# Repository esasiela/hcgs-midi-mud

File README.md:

# hcgs-midi-mud

This is the firmware, schematics, and artwork files for an Arduino-based MIDI Step Sequencer.

Details about the behavior, design, software, and hardware are at [Hedge Court](https://www.hedgecourt.com/robots/grumpenspiel/midi-mud/).

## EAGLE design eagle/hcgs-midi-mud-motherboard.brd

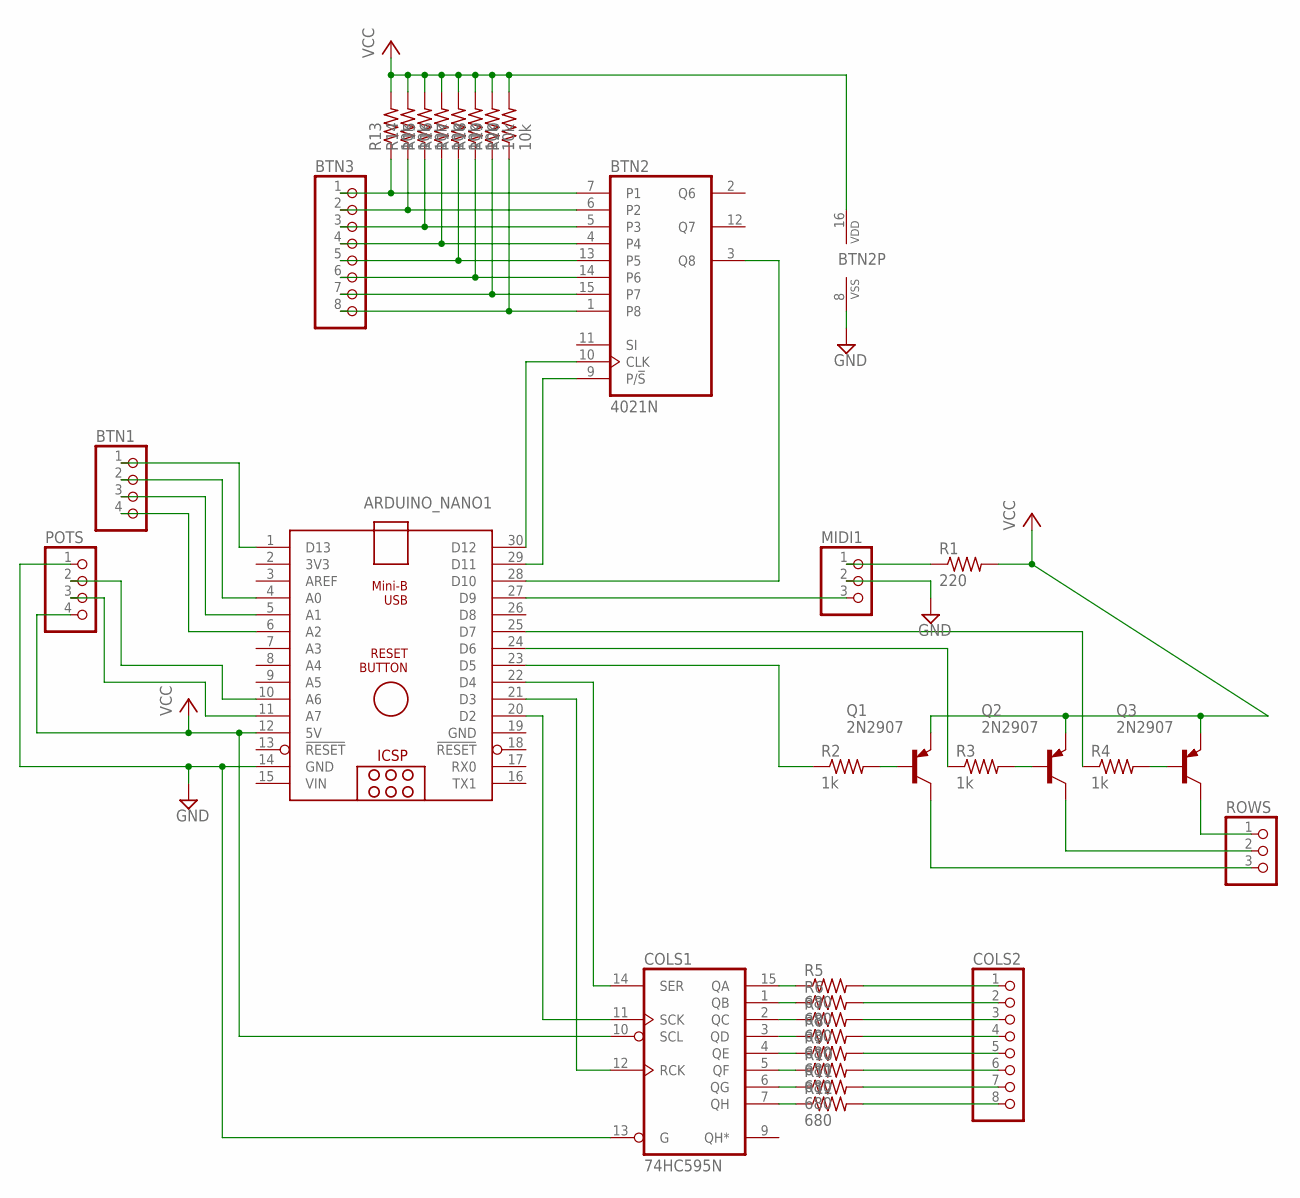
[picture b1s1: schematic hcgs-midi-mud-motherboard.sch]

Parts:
ARDUINO_NANO1: ARDUINO_NANO_HCARDUINO_NANO_NO_HOLE; ARDUINO_NANO_NO_HOLE
BTN1: PINHD-1X4; 1X04
BTN2: 4021N; DIL16
BTN3: PINHD-1X8; 1X08
COLS1: 74HC595N; DIL16
COLS2: PINHD-1X8; 1X08
MIDI1: PINHD-1X3; 1X03
POTS: PINHD-1X4; 1X04
Q1, Q2, Q3: 2N2907; TO92-EBC-OVAL
R1: 220; 0309/12
R2, R3, R4: 1k; 0309/12
R5, R6, R7, R8, R9, R10, R11, R12: 680; 0309/12
R13, R14, R15, R16, R17, R18, R19, R20: 10k; 0309/12
ROWS: PINHD-1X3; 1X03

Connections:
GND: ARDUINO_NANO1.14 (GND), ARDUINO_NANO1.19 (GND), BTN2.8 (VSS), COLS1.8 (GND), COLS1.13 (G), MIDI1.2, POTS.1
unnamed: ARDUINO_NANO1.1 (D13), BTN1.1
unnamed: ARDUINO_NANO1.4 (A0), BTN1.2
unnamed: ARDUINO_NANO1.11 (A7), POTS.3
unnamed: ARDUINO_NANO1.10 (A6), POTS.2
unnamed: ARDUINO_NANO1.5 (A1), BTN1.3
unnamed: ARDUINO_NANO1.6 (A2), BTN1.4
unnamed: Q1.B, R2.2
unnamed: MIDI1.1, R1.1
unnamed: Q2.B, R3.2
unnamed: ARDUINO_NANO1.27 (D9), MIDI1.3
unnamed: Q3.B, R4.2
unnamed: ARDUINO_NANO1.23 (D5), R2.1
unnamed: ARDUINO_NANO1.24 (D6), R3.1
unnamed: ARDUINO_NANO1.25 (D7), R4.1
unnamed: Q1.C, ROWS.3
unnamed: Q2.C, ROWS.2
unnamed: Q3.C, ROWS.1
unnamed: COLS1.15 (QA), R5.1
unnamed: COLS1.1 (QB), R6.1
unnamed: COLS1.2 (QC), R7.1
unnamed: COLS1.3 (QD), R8.1
unnamed: COLS1.4 (QE), R9.1
unnamed: COLS1.5 (QF), R10.1
unnamed: COLS1.6 (QG), R11.1
unnamed: COLS1.7 (QH), R12.1
unnamed: COLS2.1, R5.2
unnamed: COLS2.2, R6.2
unnamed: COLS2.3, R7.2
unnamed: COLS2.4, R8.2
unnamed: COLS2.5, R9.2
unnamed: COLS2.6, R10.2
unnamed: COLS2.7, R11.2
unnamed: COLS2.8, R12.2
unnamed: ARDUINO_NANO1.20 (D2), COLS1.11 (SCK)
unnamed: ARDUINO_NANO1.21 (D3), COLS1.12 (RCK)
unnamed: BTN2.1 (P8), BTN3.8, R20.1
unnamed: ARDUINO_NANO1.22 (D4), COLS1.14 (SER)
unnamed: BTN2.15 (P7), BTN3.7, R19.1
unnamed: BTN2.14 (P6), BTN3.6, R18.1
unnamed: BTN2.13 (P5), BTN3.5, R17.1
unnamed: BTN2.4, BTN3.4, R16.1
unnamed: BTN2.5 (P3), BTN3.3, R15.1
unnamed: BTN2.6 (P2), BTN3.2, R14.1
unnamed: BTN2.7 (P1), BTN3.1, R13.1
unnamed: ARDUINO_NANO1.30 (D12), BTN2.10 (CLK)
unnamed: ARDUINO_NANO1.28 (D10), BTN2.3 (Q8)
unnamed: ARDUINO_NANO1.29 (D11), BTN2.9 (P/!S)
VCC: ARDUINO_NANO1.12 (5V), BTN2.16 (VDD), COLS1.10 (SCL), COLS1.16 (VCC), POTS.4, Q1.E, Q2.E, Q3.E, R1.2, R13.2, R14.2, R15.2, R16.2, R17.2, R18.2, R19.2, R20.2
VIN: ARDUINO_NANO1.15 (VIN)

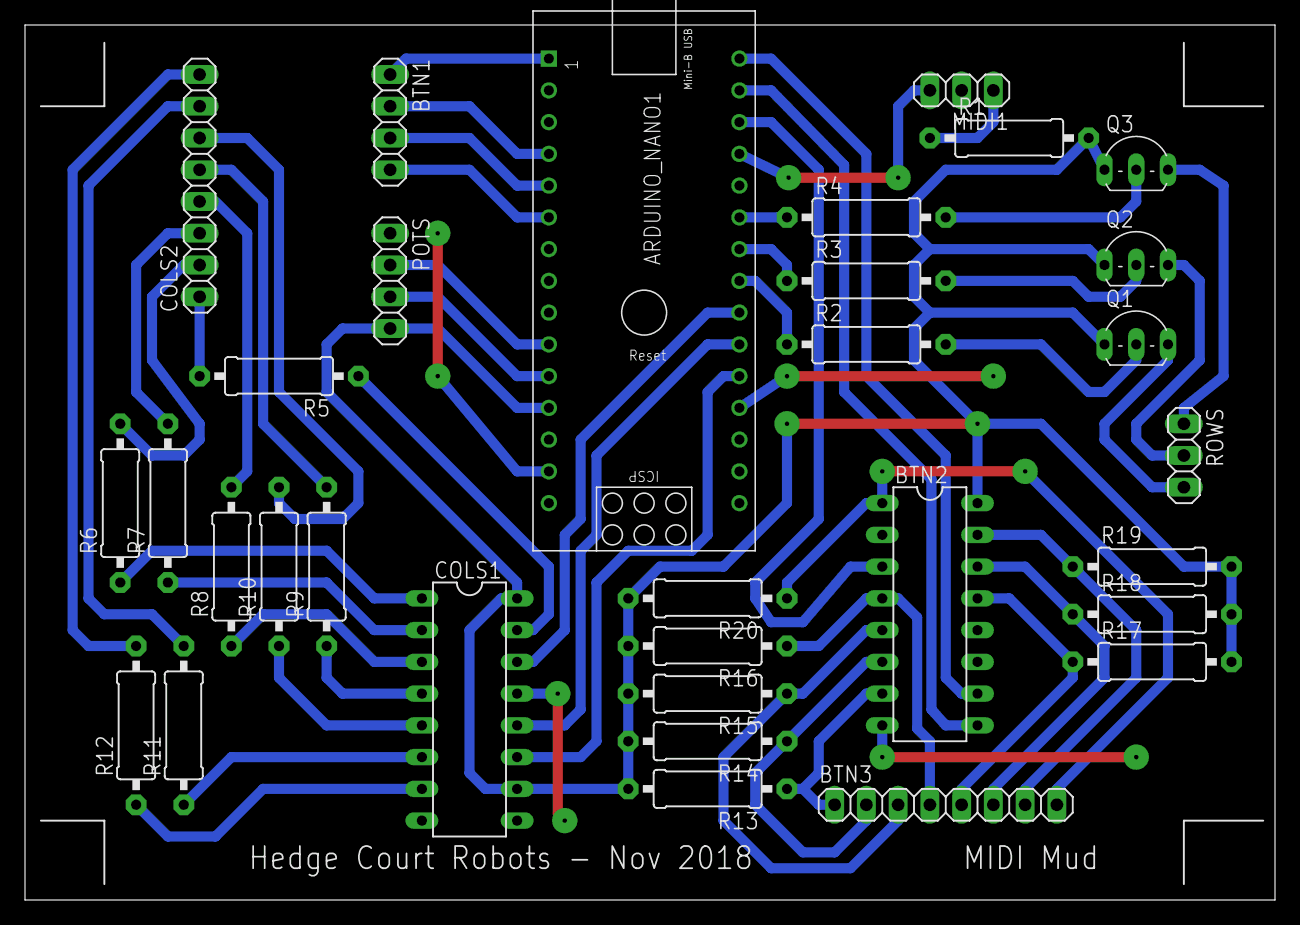
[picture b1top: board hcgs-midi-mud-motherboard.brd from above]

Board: 2 copper layers, 100.0 x 70.0 mm, 32 parts (0 on the bottom side), 49 nets.

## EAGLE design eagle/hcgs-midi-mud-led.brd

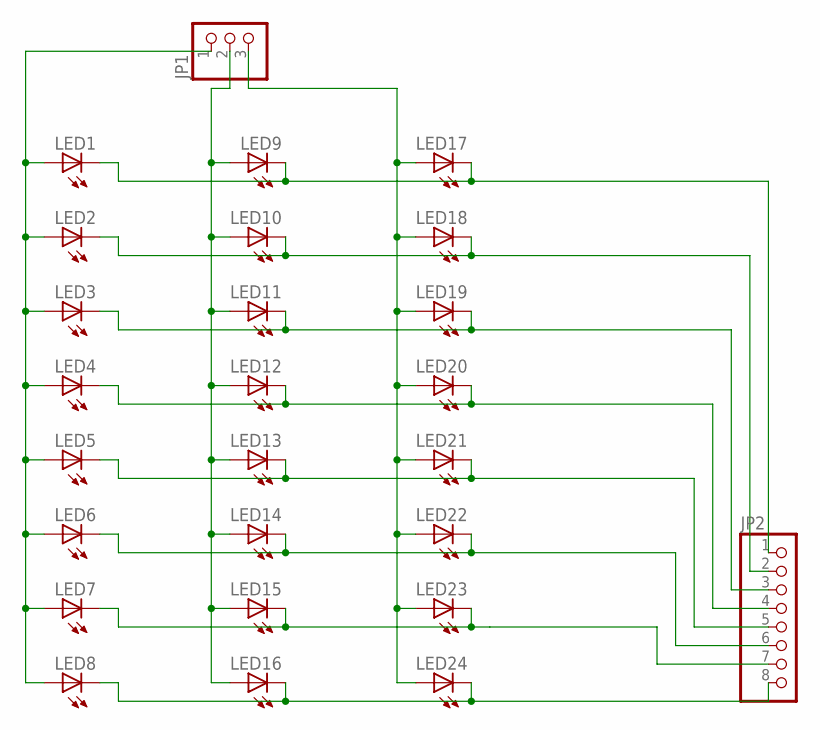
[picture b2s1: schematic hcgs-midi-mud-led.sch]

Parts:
JP1: PINHD-1X3; 1X03
JP2: PINHD-1X8; 1X08
LED1, LED2, LED3, LED4, LED5, LED6, LED7, LED8, LED9, LED10, LED11, LED12, LED13, LED14, LED15, LED16, LED17, LED18, LED19, LED20, LED21, LED22, LED23, LED24: LED5MM

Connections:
unnamed: JP1.1, LED1.A, LED2.A, LED3.A, LED4.A, LED5.A, LED6.A, LED7.A, LED8.A
unnamed: JP1.2, LED9.A, LED10.A, LED11.A, LED12.A, LED13.A, LED14.A, LED15.A, LED16.A
unnamed: JP1.3, LED17.A, LED18.A, LED19.A, LED20.A, LED21.A, LED22.A, LED23.A, LED24.A
unnamed: JP2.1, LED1.K (C), LED9.K (C), LED17.K (C)
unnamed: JP2.2, LED2.K (C), LED10.K (C), LED18.K (C)
unnamed: JP2.3, LED3.K (C), LED11.K (C), LED19.K (C)
unnamed: JP2.4, LED4.K (C), LED12.K (C), LED20.K (C)
unnamed: JP2.5, LED5.K (C), LED13.K (C), LED21.K (C)
unnamed: JP2.6, LED6.K (C), LED14.K (C), LED22.K (C)
unnamed: JP2.7, LED7.K (C), LED15.K (C), LED23.K (C)
unnamed: JP2.8, LED8.K (C), LED16.K (C), LED24.K (C)

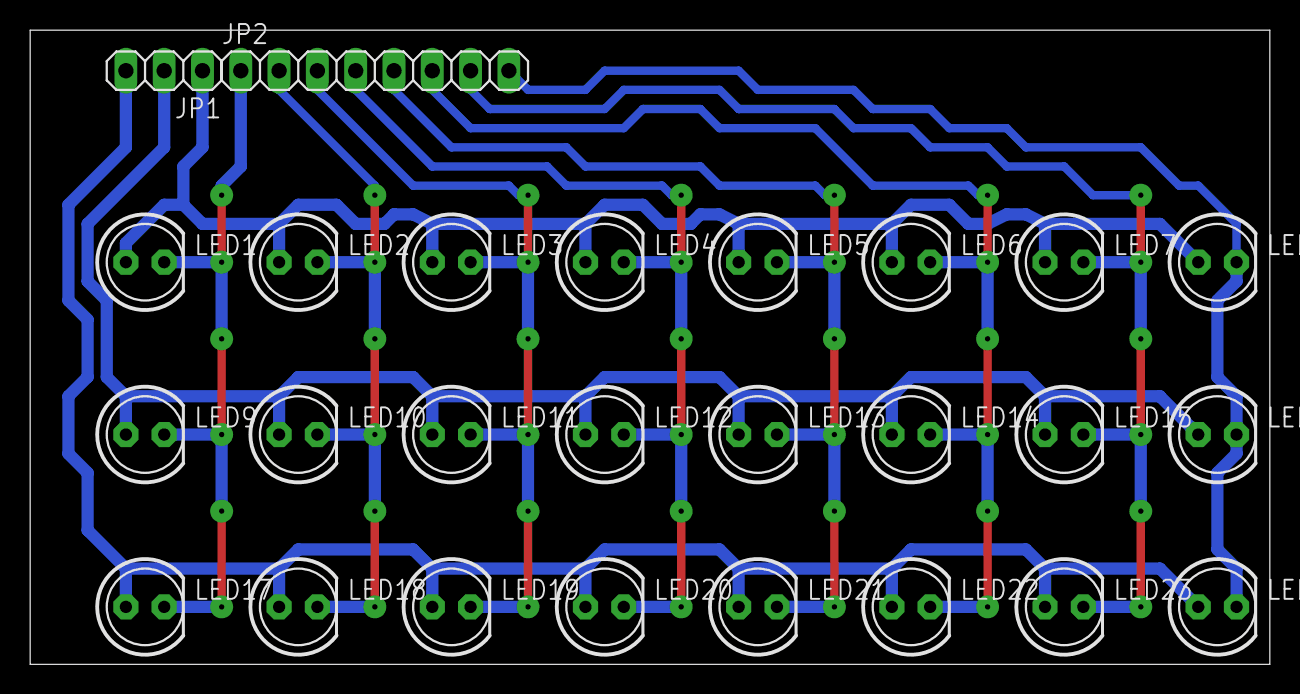
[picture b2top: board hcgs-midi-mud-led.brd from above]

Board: 2 copper layers, 82.2 x 42.1 mm, 26 parts (0 on the bottom side), 11 nets.

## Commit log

2018-12-18 added serial interface for EEPROM config
